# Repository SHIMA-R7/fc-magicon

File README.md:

# FC-MAGICON

Waveshare Core2350B(RP2350B)1枚で作るファミコン用カセット。

ツインファミコン＋ブラウン管での実機表示。[カートリッジ・画面の接写・テスト風景を見る（写真4枚）](docs/photos_20261018.md)。

- PRG・CHR を RP2350B がリアルタイムにエミュレート(マジコン。NROM/CNROM/UNROM/MMC1/MMC3 などをファームで実装)
- NSF 再生(バンク切り替え・WRAM 対応。拡張音源は PWM で46番に混ぜる)
- PC→FC 画面転送(PPU の読み出しに直接応答する FC-PICO 方式)

## 2026-11-08の更新

- **カセットへのPC有線接続なしで更新**：ESP32-C6経由のWi-Fi→USBでファームとFCPVメディアを転送・照合し、DP100による電源再投入で再生。[導入・更新手順](docs/c6-usb-update.md)。
- **SWD経由の導入・復旧**：C6 GPIO6/7を利用し、Wi-Fi経由でOpenOCDから書き込み・照合。[SWD手順](docs/c6-swd-programming.md)。
- **全編8fps映像＋FC本体DAC音声**：約67秒の全編を実機確認。RAM常駐の6502ドライバーが224 CPUサイクル間隔で `$4011` へ書き込み、歌声・伴奏を再生。
- **OLED＋追加パスコンで再試験**：無線更新、全編再生2回、再起動3回の接続に成功。ただし最初の1回はWi-Fi接続に失敗しており、完全な起動安定性やパスコンの効果は未確定。[測定値・確認範囲](docs/wifi-update-validation-20261108.md)。
- 公開対象はソースと検証記録。動画・音声素材、それらを含むファーム、Wi-Fi認証情報は含めません。

## 2026-10-31の更新

- **新基板の元配線で全編動画を再生**：全1,939コマ・8fpsの進行と、FC給電だけでの起動を確認。[検証記録](docs/new_board_video_20261031.md)。
- **動画と本体音源の同時再生**：ユーザー提供MIDIを矩形波2音＋三角波へ変換し、動画と一緒に再生。本体音源の発音はユーザーが確認した。[方式・ビルド手順・確認範囲](docs/native_apu_video_20261031.md)。
- **一時的な横縞への対策**：画面切り替えの制御情報を事前生成してCPUへ高速応答する比較版で、問題の場面の横縞が再現せず、248秒の全編試験を完走。全画素の無欠損や旧基板の故障原因まで保証する結果ではない。
- MIDI、動画、録画、楽曲を含むヘッダー・UF2は公開しない。公開ソースでは自分のMIDIを外部ファイルとして指定する。

## 2026-10-18時点の達成事項

- **単独動画再生の目標達成**：PC非接続のツインファミコンで、全編99秒・8fpsのカラー映像と音声を再生。ユーザーが完成を確認した。著作物である動画素材・音声・それらを含むUF2は公開しない。
- **ESP32-C6無線リモートデスクトップ**は、PCの映像・音声とFC入力をWi-Fi経由でやりとりします。ツインファミコン給電のみでの起動と映像転送を実機で確認しました。[配線・ビルド・4:3全画面設定](docs/wifi-remote-desktop.md)
- **USBリモートデスクトップでブルアカ操作に成功**：FMV（Windows 11）から映像・音声を転送し、入力をPCへ反映。通常のWindowsでは動くのにブルアカでFCパッド／Nanoマウスが効かない問題は、ユーザーが**送信アプリを管理者として実行して解消を確認**した。この環境では送信アプリを右クリック→管理者として実行する。
- **操作機能**：SELECTで通常→中段ズーム（512×480）→最大ズーム（256×240）。FCキーボード対応。NanoのUSBシリアルによるSFCマウス移動・左右クリックも追加し、元のPico向け通信は維持した。
- **終了動作**：受信r2は送信アプリ停止時と切断／受信停止時に、音声を止めて待機画面へ戻る。
- **配布**：[Windows送信アプリr2.3](https://github.com/SHIMA-R7/fc-magicon/releases/tag/usb-sender-r2.3-20261018)、[FMVの使い方](docs/fmv_usb_sender_r2_20261017.md)、[Nanoマウス](docs/nano_sfc_mouse_20261018.md)。送信アプリと受信ファームは別の版番号。
- **映像崩れの切り分け**：同じファームの照合は通り、最小診断ではROM読み出し3508回中不一致0。ユーザーがカセット／基板を動かすと崩れが消えることを確認し、接触状態が強く疑われる。音声・キーボードの処理だけが原因とした途中の見立ては確定していない。接触箇所と長時間安定性は引き続き確認が必要。
- **次の段階**：ESP32-C6による無線転送。現在の修正済み映像・音声との統合、電源容量、逆給電防止を確認してから進める。

[達成状況と実機確認](docs/milestones_20261018.md) ／ [今後の計画](docs/roadmap_after_video_stability_20261015.md)

### 2026-10-13時点の経過（以下の未確認事項の一部は、その後上記まで進展）

- **実機確認**：NEWファミコンで診断画像、F1 Race、スーパーマリオブラザーズが動作。SMB1はユーザーが1-2までプレイし問題なし。MMC3のマリオ3は遊べる段階まで進んだが、下部表示の化けが残る。
- **リモート表示**：実機でPC画面の灰色・全画面表示を確認。高画質カラー・動画・音声の同時動作はまだ実機未確認。
- **オフライン検証**：MMC3のIRQテストと同一入力3,900フレームの比較、カラー動画の連続表示、実際のC音声リングを使った通信負荷試験を追加。エミュから描画位置を得る試験は、実機の成功を保証しない。
- **修正**：MMC3リロード要求の世代管理、リモートのタイル番号保持、12ドットカーソル、マウス感度半減、音声を映像の間に送れる任意の分割プロトコル。
- **未解決**：実機のPPU位置検出・応答期限、タイル圧縮の画質低下と8フレームNT更新中の混在、実機のMMC3 IRQ/CHR更新、カラー・音声・動画の安定性。
- 検証記録：[MMC3](docs/mmc3_sequence_validation_20261013.md)、[動画・音声](docs/remote_video_audio_validation_20261013.md)、[PVの30秒検証](docs/youtube_transfer_30s_20261013.md)。ゲームROMや動画素材は公開しない。
- [先例を参考にした最適化](docs/reference_optimization_20261013.md)：PCのカラー変換を画素同一のまま平均26.9ms→14.8msへ短縮。ネームテーブル/CHRアドレスだけからの位置検出もエミュで確認（実機のDMA経路への接続はまだ）。同じPVを再検証済み。
- 未書込みの実験版：[分割受信・小カーソルのUF2](firmware/out-direct-pio-diagnostic/magicon-remote-full-smallcursor-chunked.uf2)。`remote_pc.py --chunked` はこの新受信ファーム専用。従来プロトコルは引き続き使用できる。

## カートリッジの外観

光沢ラベルを貼ったカートリッジ。開口部からCore2350B2や各操作部へアクセスできる。[実機写真の一覧](docs/photos_20261018.md)。

## 基板と既存機能

- **基板 rev0.2 の設計が完了(2層、DRC エラー0・未接続0)。発注済み（2026-10-10 ユーザー確認）。**
- 発注後の保護対策: [対策・後付け回路・検証手順](docs/post_order_protection.md)。保護版ファームは `firmware/out-protected/`。現物での電源・バス波形検証は未実施。
- ファームウェア: 動作確認用の `bus_test`(CPU バスでテスト ROM を返して音を鳴らす)と `chr_test`(PPU に CHR を返して画面に格子模様を出す)、
  マジコン本体の `magicon`(.nes を動かす。NROM/MMC1/UxROM/CNROM/MMC3/AxROM、PRG + CHR 384KB まで)を作成、ビルド済み。各モードの実機確認範囲は上記を参照。[`firmware/`](firmware/README.md)
- rev0.1 からの変更: USB の予備ランド(J6)、拡張音源の音量用の半固定抵抗 VR1(KOA KVSF637AC104)を追加、
  電源・音声の配線を太くした(+5V 0.8mm、VBUS 0.6mm、GND 0.5mm、+3V3 0.4mm、音声 0.4mm)、J5 の 12〜14番を GND に。
- ガーバー: [`kicad/FC-MAGICON_gerber_r0.2.zip`](kicad/FC-MAGICON_gerber_r0.2.zip)(発注の指定は下の「基板の発注」)
- 仕様書: [`docs/hardware_spec.pdf`](docs/hardware_spec.pdf)(rev0.2)

| 正面(部品面、本体の手前) | 背面 |
|---|---|
|  |  |

## ファイル

| パス | 内容 |
|---|---|
| `kicad/gen_schematic.py` | 回路図の生成スクリプト(`python gen_schematic.py` → `FC-MAGICON.kicad_sch`) |
| `kicad/gen_footprints.py` | カセット端子と半固定抵抗(KOA KVSF637A)のフットプリントを生成 |
| `kicad/build_pcb.py` | 基板の部品配置(`place`)、配線の取り込みと GND ベタ(`import`)、一部の配線のやり直し(`reroute`) |
| `kicad/route.py` | Freerouting で自動配線(線幅のクラスを付ける) |
| `kicad/add_part.py` / `sync_nets.py` / `hand_route.py` | 配線済みの基板に部品を足す / パッドのネットを回路図に合わせる / 1本だけ手で引く |
| `kicad/export_gerbers.ps1` | DRC がエラー 0 のときだけガーバーを出して zip にする |
| `kicad/bom.py`, `print_bom.ps1` | 部品表(`bom.csv`)の作成と印刷 |
| `kicad/print_core2350b_pinmap.ps1`, `print_fit_check.ps1` | Core2350B のピン照合シート、実寸の現物合わせシートの印刷 |
| `kicad/check_nets.py`, `drc_summary.py` | 回路図の簡易チェック、DRC レポートの集計 |
| `3d/` | 基板の STEP(`FC-MAGICON_r0.2_parts.step` 部品あり / `_board.step` 基板だけ / `FC-MAGICON.step` 部品あり版を Autodesk で読み込んで書き出し直したもの)。`make_models.py` → `export_step.py`(KiCad の Python)で作り直す。原点は基板の左上、Y は上向き(基板は Y 0〜-65.8) |
| `kicad/print_part_guide.ps1` | 部品案内図(表・裏、原寸)の印刷 |
| `case/label/` | カセット表面のシール(`make_label.py` → `label.png`、`print_label.ps1` で A4 に印刷)。99 x 60.6mm、ケースの穴(J3/J5/J6/VR1/SW/Core2350B2)は原寸。L 判の光沢紙にきれいに刷る時は `make_label.py --px 48 --out label_print.png` → `powershell.exe -File print_label_photo.ps1`(光沢紙・写真品質) |
| `case/*.py` | ケースの元データ(下記)の寸法を調べたスクリプトと、基板の部品の占有範囲(`parts.json`) |
| `docs/` | ハードウェア仕様書(`build_spec.py` と `kicad/gen_spec_tables.py` で作る) |

KiCad 10、Freerouting 2.4.1 を使用。KiCad の Python(pcbnew)で実行するスクリプトと、ふつうの Python で実行するスクリプトがある(各ファイルの先頭に記載)。

## ライセンス

独自コードはMIT(`LICENSE`)。第三者のエミュレーターや検証用パッチはそれぞれのライセンスに従う。[第三者コードと検証コア](firmware/sim/THIRD_PARTY.md)を参照。外形の参考にしたデータ(下記「カセット外形の参考データ」)はこのリポジトリに含めていない。

## ピン割り当て

| GPIO | 信号 | カセット端子 | 備考 |
|---|---|---|---|
| 0-7 | CPU D0-D7 | 43,42,41,40,39,38,37,36 | |
| 8-22 | CPU A0-A14 | 13,12,11,10,9,8,7,6,5,4,3,2,33,34,35 | A0から連続 |
| 23 | /ROMSEL | 44 | |
| 24 | CPU R/W | 14 | |
| 25 | M2 | 32 | |
| 26-33 | PPU AD0-AD7 | 26,27,28,29,60,59,58,57 | /RD直前はアドレス下位、その後データ |
| 34-38 | PPU A8-A12 | 51,52,53,54,55 | 26-38で13ビット連続 |
| 39 | (基板上LED) | — | バスに使わない |
| 40 | PPU /RD | 17 | U2(74LVC245)経由 |
| 41 | PPU /WR | 47 | U2経由 |
| 42 | PPU A13 | 56 | U2経由 |
| 43 | CIRAM A10 出力 | 18 | JP1を閉じたとき |
| 44 | 拡張音源 PWM | 46へ混ぜる | |
| 45 | /IRQ 駆動 | 15 | Q1(NPN)でオープンコレクタ |
| 46 | 本体5V検出 | 30,31 を分圧 | Highになるまでバスに出力しない |

- PIO の32本窓: CPU 用ブロックは GPIO0-31、PPU 用ブロックは GPIO16-47。
- GPIO0-38 は 5V トレラント。GPIO40-47 は ADC 兼用で **5V 非トレラント**。
- PPU A0-A7(19-25, 50番)はつながない。
- CIRAM /CE(48)は /A13(49)に直結(R1 0Ω)。
- ミラーリング: JP1(MCU)/ JP2(A10=垂直)/ JP3(A11=水平)のどれか1つだけ閉じる。

## テスト用のランド(2.54mmピッチ、ピンヘッダー・ソケットどちらも可)

基板は規格(56.8mm)より 9mm 高い(90 × 65.8mm)。

**J4: カセット60ピン全部(2x30)** — 差し込み部のすぐ上(2026-09-26、2層に収めるため上辺から移動)
各列がカセット端子の真上にあり、端子から J4 まではほぼ真上への短い配線。上の列 = 31〜60番、下の列 = 1〜30番。
部品面(本体の手前)から見て左端が 1/31番、右端が 30/60番(シルクに列番号あり)。
RP2350 では使わない PPU A0-A7(19〜25番、50番)も出している。

**J5: 基板内部の信号(2x8)** — 上辺
部品面から見て左端が 1/2番。奇数番 = 下の列、偶数番 = 上の列。

| ピン | 信号 | ピン | 信号 |
|---|---|---|---|
| 1 | PPU /RD(3.3V、U2の後) | 2 | PPU /WR(3.3V) |
| 3 | PPU A13(3.3V) | 4 | CIRAM A10(GPIO43の出力) |
| 5 | 拡張音源 PWM(GPIO44) | 6 | PWM の RC フィルタの後 |
| 7 | /IRQ 駆動(GPIO45) | 8 | 本体5V検出(GPIO46) |
| 9 | +3.3V | 10 | VBUS(モジュールの電源) |
| 11 | CIRAM A10(18番へ行く線) | 12 | ライン出力(47kの前) |
| 13 | Q1 ベース | 14 | ライン出力(100Ωの後) |
| 15 | GND | 16 | GND |

TP1〜TP5(/RD、D0、M2、/ROMSEL、GND)はオシロのプローブ用。

## 基板発注前に確認すること

1. ~~**カセット端子の電源・音声・制御ピン。**~~ → 2026-09-26 ユーザーが麻雀カセット・本体で確認、問題なし。 信号線51本はダンパー(`../FC`)で実機確認済み。
   1,16(GND)・30,31(+5V)・15(/IRQ)・18(CIRAM A10)・45,46(音声)・47(/WR)・48(CIRAM /CE)・49(/A13)は
   nesdev の資料によるので、麻雀カセットと本体で導通を確認する。
2. ~~**45/46 の向き。**~~ → 2026-09-26 確認済み。 本体(HVC-CPU-07)で、どちらが 2A03 の音声回路につながっているか確認する。
3. ~~**本体の /IRQ プルアップの有無。**~~ → 2026-09-26 確認済み。 無ければ R6(10k)を実装する。
4. ~~Core2350B のヘッダー配置~~ → 2026-09-26 に照合シート(`kicad/print_core2350b_pinmap.ps1`)で、実物のシルクと全ピン一致を確認した。
   25.4mm角、外周2列、2.54mmピッチ。左・下・右・上がそれぞれ P1・P3・P4・P2。
5. ~~カセットの基板厚とエッジの寸法~~ → 参考データ(下記)から、厚み 1.2mm・差し込み部 78.4 × 10.7mm。
   正確に作るのはスロットに刺さる部分だけでよい。残りの外形は自由にし、ケースは3Dプリント(Bambu P1S)で作る。
6. **試作での実測。** PPU の /RD が下がってからデータを返すまでの時間。仮配線はせず、この基板(TP1〜TP5)で測る方針に変更。

## 基板の発注(JLCPCB)

`kicad/FC-MAGICON_gerber_r0.1.zip` をアップロードする(`kicad/export_gerbers.ps1` で作り直せる。DRC にエラーがあると止まる)。

| 項目 | 指定 |
|---|---|
| 層数 | 2 |
| 厚み | **1.2mm**(ファミコンのスロットに合わせる。1.6mm は入らない) |
| 金メッキ端子 | Gold Fingers: Yes |
| 面取り | 差し込み側 45°(finger chamfer) |
| 表面処理 | 金メッキ端子と組み合わせられるもの(発注画面で ENIG 指定が必要か確認する) |
| 数量 | 5枚(最小) |

- 外形は 90 × 65.8mm。差し込み部(78.4 × 10.7mm)の両脇は切り欠き。
- 端子部のレジストは、端子の上端から 0.6mm 上で止めてある(付け根側の配線はレジストで覆う)。

## カセット外形の参考データ(`ref/`)

| 出典 | ライセンス | 中身 |
|---|---|---|
| [Gumball2415/NES-Famicom-Cartridge-Dimensions](https://github.com/Gumball2415/NES-Famicom-Cartridge-Dimensions) | TAPR OHL 1.0 | HVC-TGROM-01 / HVC-CNROM-256K-01 の外形(KiCad)と FreeCAD 3Dモデル(.FCStd、STEP書き出し可) |
| [Keitark/fc-rom-vomitter](https://github.com/Keitark/fc-rom-vomitter) | ハード: CC BY-SA 4.0 | 60ピンのエッジのフットプリントと、実際に製造したファミコン用基板 |

- 標準のファミコン基板: 幅 90.0mm × 高さ 56.8mm(差し込み部 78.4 × 10.7mm を含む)、**厚み 1.2mm**、ピッチ 2.54mm。
- 市販カセットは 1〜30番がラベル面(本体の手前)。この基板は部品面(F.Cu)を手前に向けたので、F.Cu = 1〜30番、B.Cu = 31〜60番。
- ピン配置は fc-rom-vomitter の表とも一致した(30/31=+5V、1/16=GND、45=本体からの音声、46=本体へ戻す音声、48/49=/A13)。
- ファイルをそのまま流用する場合は、元のライセンスに従うこと。寸法(事実)を参照して自作するならその限りではない。

## ケース(3Dプリント)の元データ

[printables 860420「Nintendo Famicom Cartridge Shell」](https://www.printables.com/model/860420-nintendo-famicom-cartridge-shell)(CC BY 4.0)。
これは [masible/famicom-everdrive-n8-shell-with-usb](https://github.com/masible/famicom-everdrive-n8-shell-with-usb)(hadessuk、CC BY)を
標準の基板向けにしたリミックスで、さらに元は Blackchamber の [Thingiverse 117607](https://www.thingiverse.com/thing:117607/)(CC BY)。
改変版を公開するときは、この3つの作者の表記を残す。

## 注意

- USB だけで給電しているときに本体のバスへ出力すると、電源の入っていない本体に電流が逆流する。
  ファームは `FC_5V_SENSE` が High になるまで、全ピンを入力にしておく。
- RP2350 のエラッタ E9 に注意。バスのピンでは内部プルダウンを使わない。
- Q1 の 2SC1815 は、平らな面から見て E-C-B。

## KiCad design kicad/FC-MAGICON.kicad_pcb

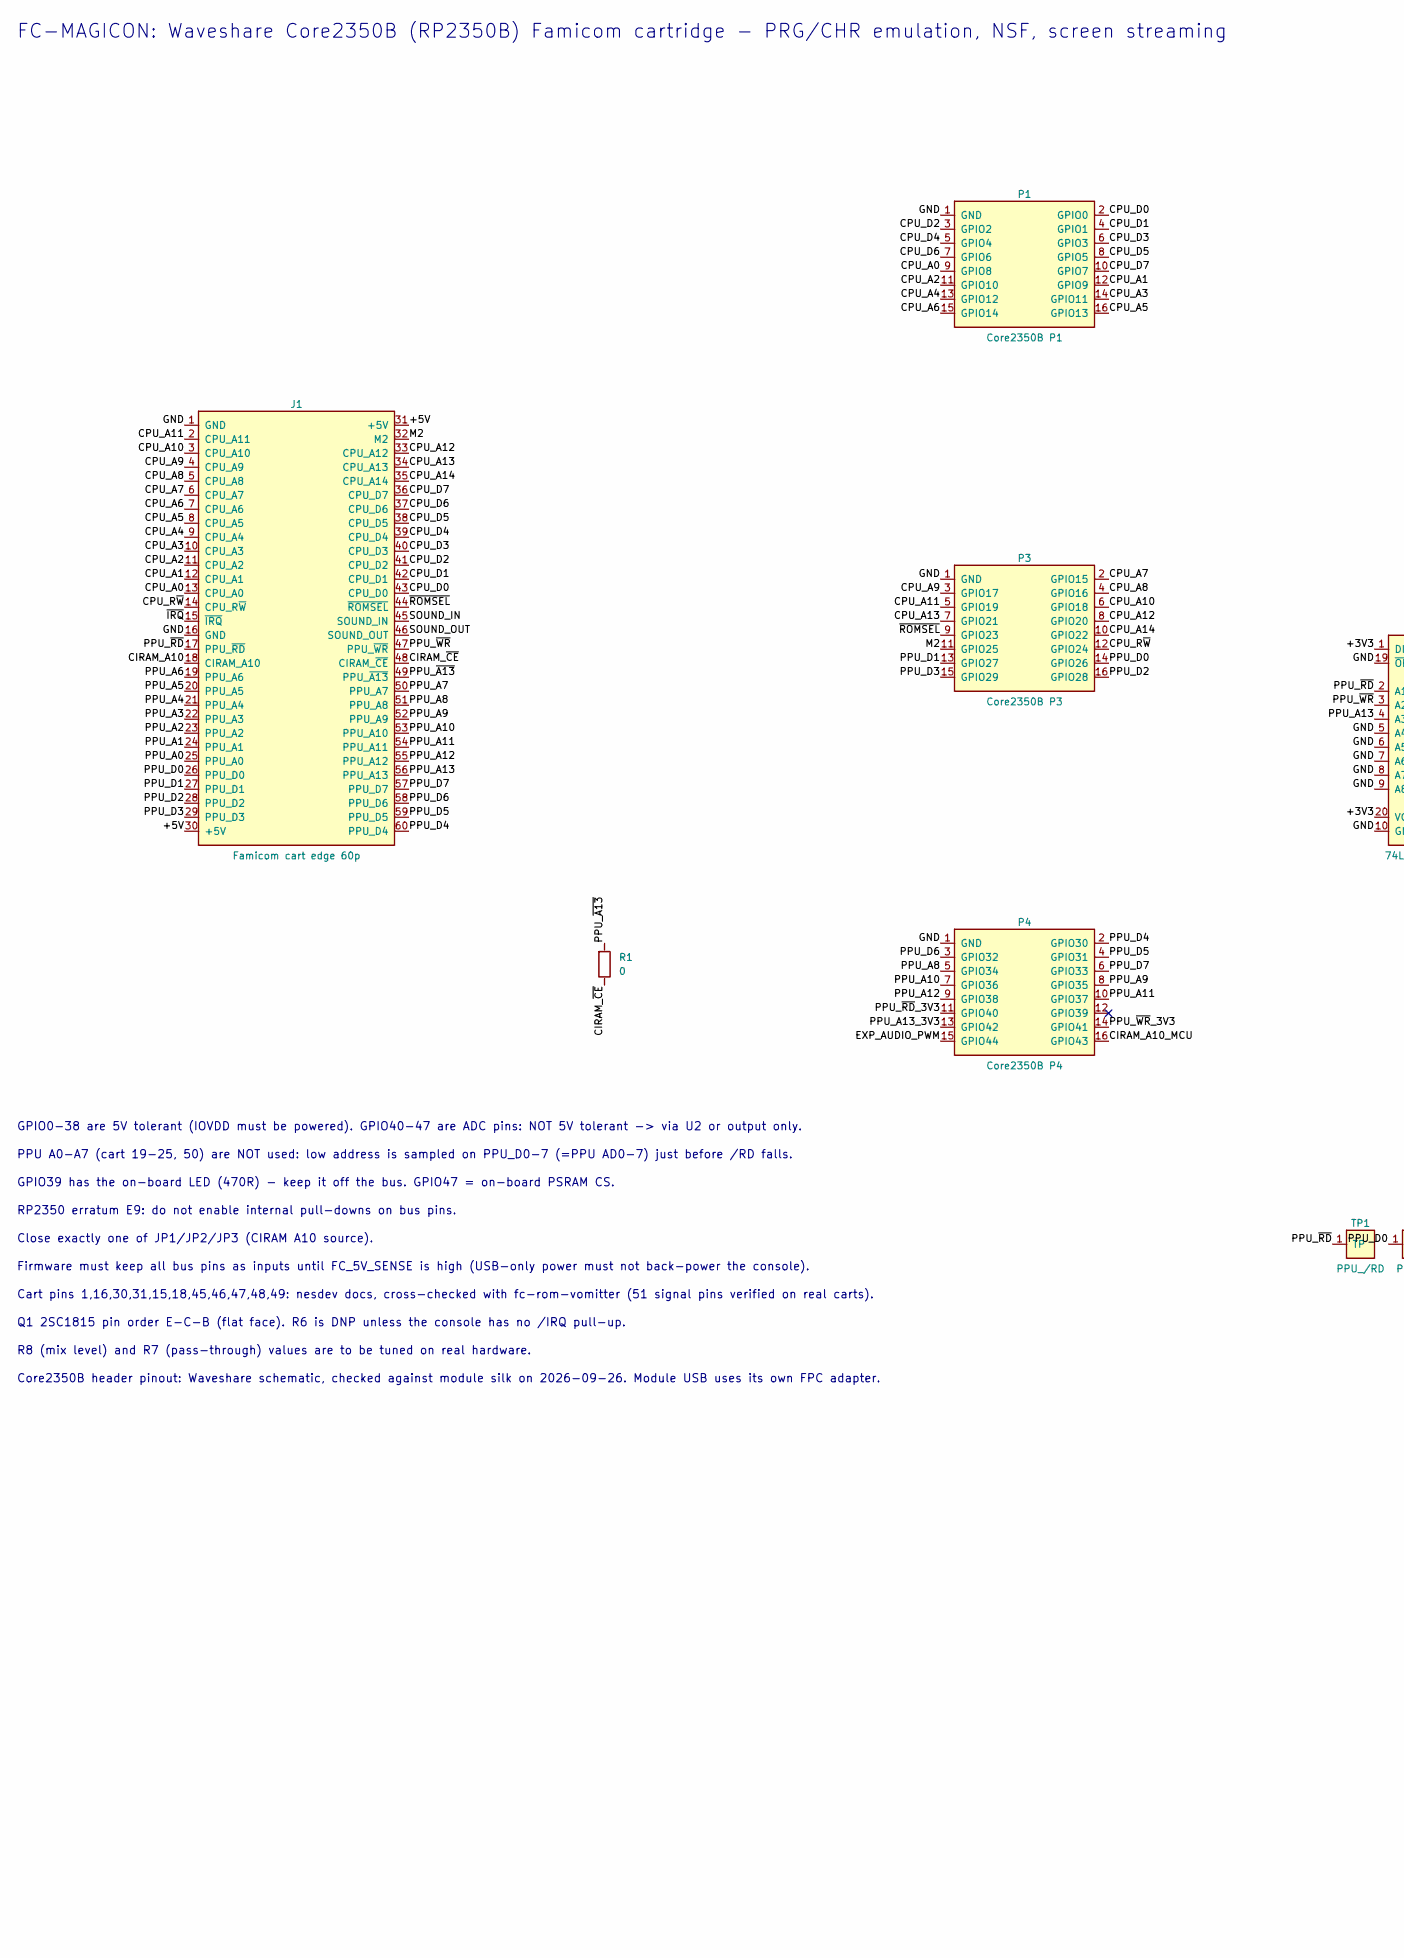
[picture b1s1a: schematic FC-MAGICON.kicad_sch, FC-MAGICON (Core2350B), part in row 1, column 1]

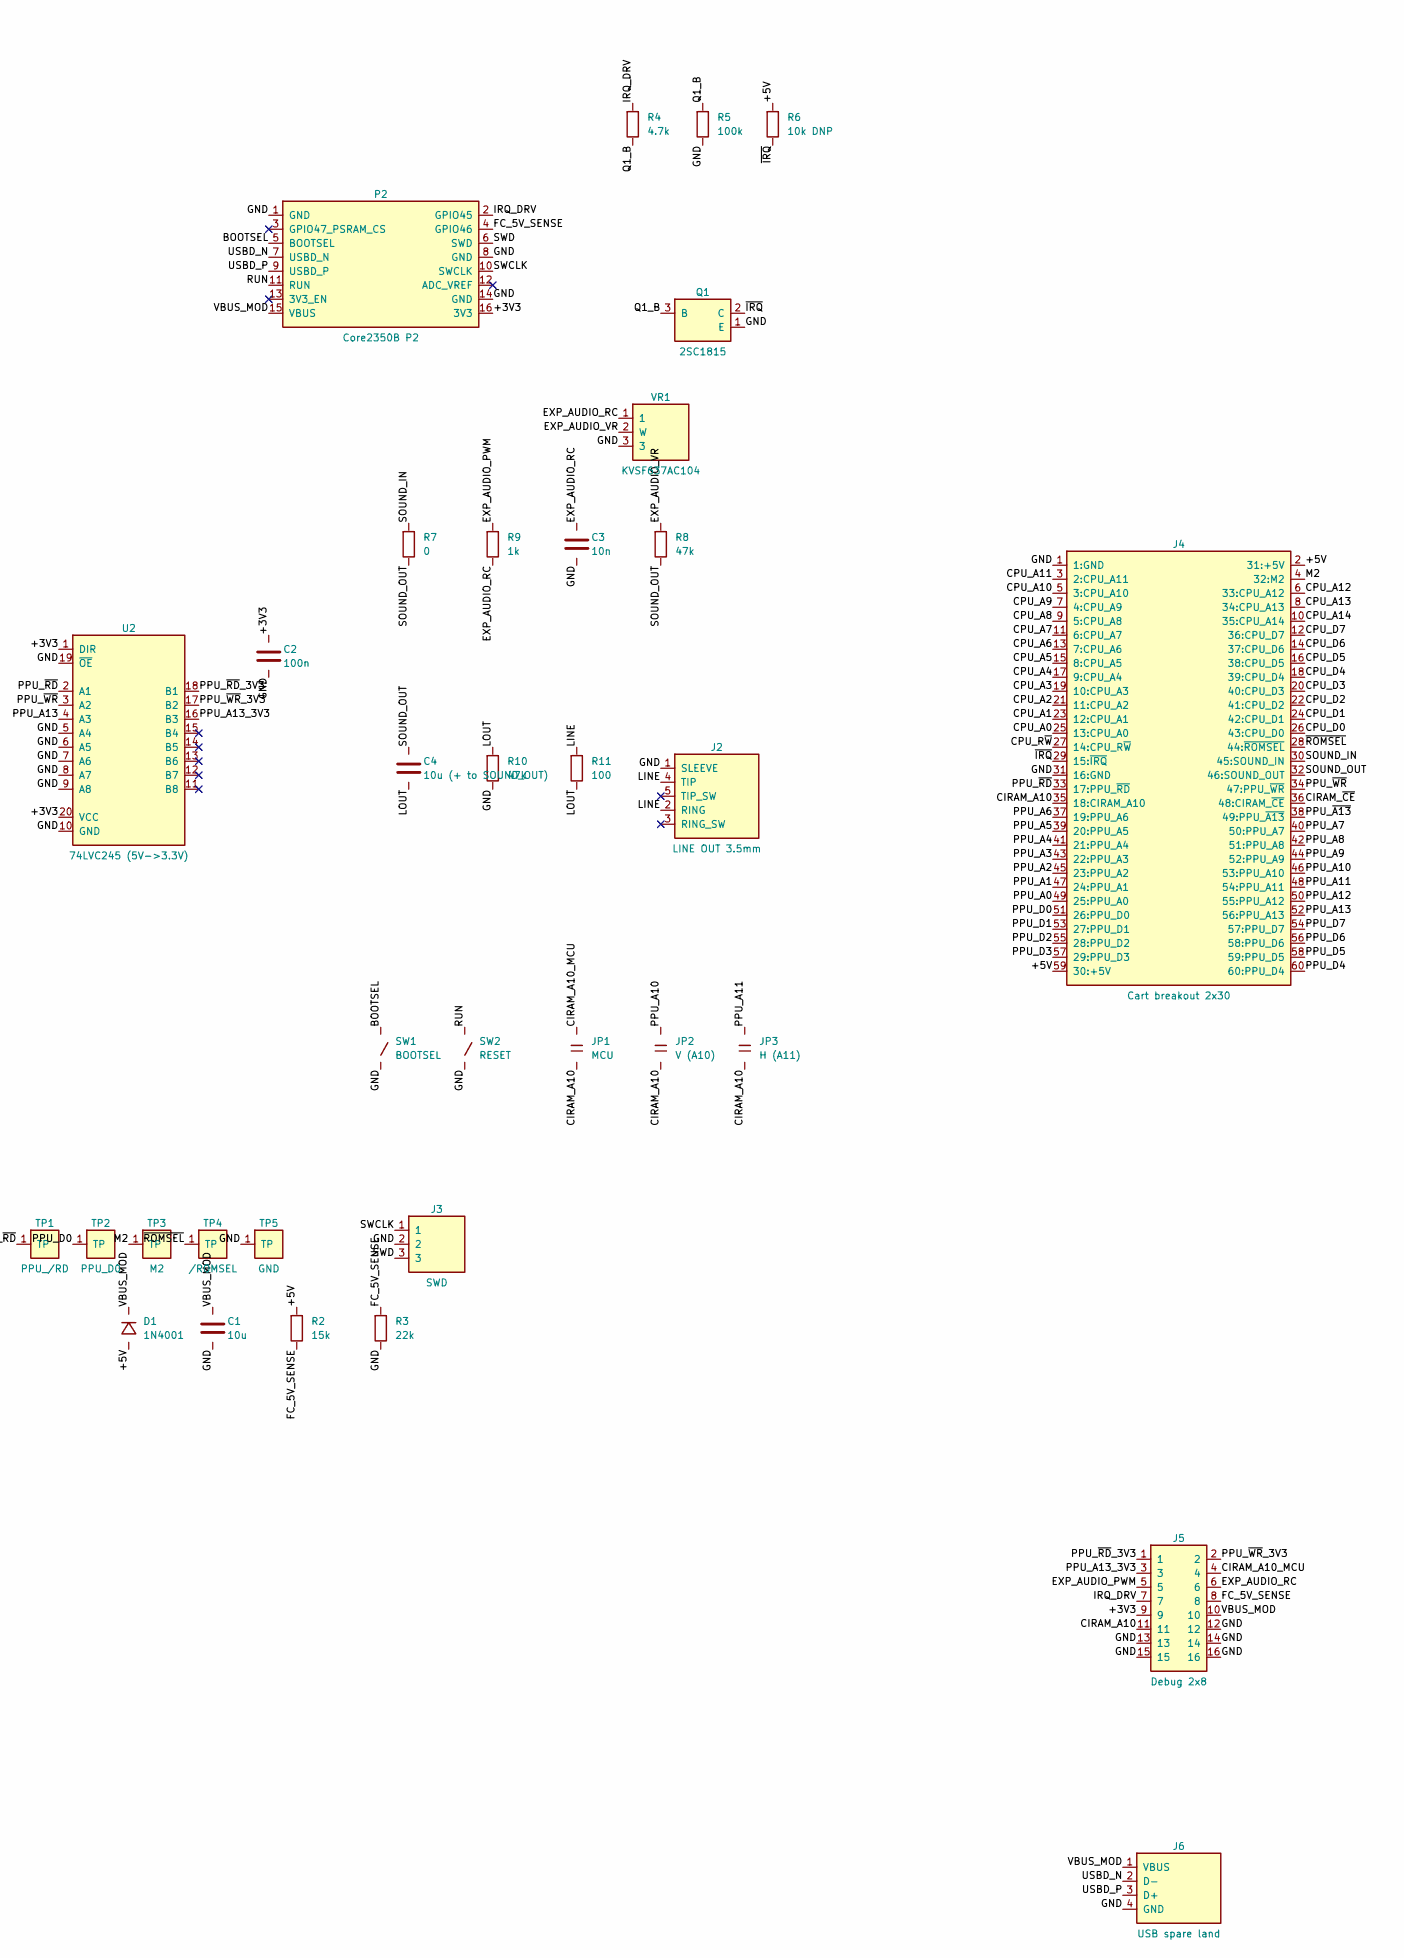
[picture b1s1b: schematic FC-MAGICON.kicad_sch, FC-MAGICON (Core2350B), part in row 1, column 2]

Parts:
C1: 10u; CP_Radial_D5.0mm_P2.00mm
C2: 100n; C_Disc_D3.0mm_W1.6mm_P2.50mm
C3: 10n; C_Disc_D3.0mm_W1.6mm_P2.50mm
C4: 10u (+ to SOUND_OUT); CP_Radial_D5.0mm_P2.00mm
D1: 1N4001; D_DO-41_SOD81_P7.62mm_Horizontal
J1: Famicom cart edge 60p; FC_Cart_Edge_60
J2: LINE OUT 3.5mm; PJ-324M
J3: SWD; PinHeader_1x03_P2.54mm_Vertical
J4: Cart breakout 2x30; PinHeader_2x30_P2.54mm_Vertical
J5: Debug 2x8; PinHeader_2x08_P2.54mm_Vertical
J6: USB spare land; PinHeader_1x04_P2.54mm_Vertical
JP1: MCU; SolderJumper-2_P1.3mm_Open_RoundedPad1.0x1.5mm
JP2: V (A10); SolderJumper-2_P1.3mm_Open_RoundedPad1.0x1.5mm
JP3: H (A11); SolderJumper-2_P1.3mm_Open_RoundedPad1.0x1.5mm
P1: Core2350B P1; PinHeader_2x08_P2.54mm_Vertical
P2: Core2350B P2; PinHeader_2x08_P2.54mm_Vertical
P3: Core2350B P3; PinHeader_2x08_P2.54mm_Vertical
P4: Core2350B P4; PinHeader_2x08_P2.54mm_Vertical
Q1: 2SC1815; TO-92_Inline_Wide
R1, R7: 0; R_Axial_DIN0207_L6.3mm_D2.5mm_P7.62mm_Horizontal
R2: 15k; R_Axial_DIN0207_L6.3mm_D2.5mm_P7.62mm_Horizontal
R3: 22k; R_Axial_DIN0207_L6.3mm_D2.5mm_P7.62mm_Horizontal
R4: 4.7k; R_Axial_DIN0207_L6.3mm_D2.5mm_P7.62mm_Horizontal
R5: 100k; R_Axial_DIN0207_L6.3mm_D2.5mm_P7.62mm_Horizontal
R6: 10k DNP; R_Axial_DIN0207_L6.3mm_D2.5mm_P7.62mm_Horizontal
R8, R10: 47k; R_Axial_DIN0207_L6.3mm_D2.5mm_P7.62mm_Horizontal
R9: 1k; R_Axial_DIN0207_L6.3mm_D2.5mm_P7.62mm_Horizontal
R11: 100; R_Axial_DIN0207_L6.3mm_D2.5mm_P7.62mm_Horizontal
SW1: BOOTSEL; SW_PUSH_6mm
SW2: RESET; SW_PUSH_6mm
TP1: PPU_/RD; TestPoint_THTPad_D1.5mm_Drill0.7mm
TP2: PPU_D0; TestPoint_THTPad_D1.5mm_Drill0.7mm
TP3: M2; TestPoint_THTPad_D1.5mm_Drill0.7mm
TP4: /ROMSEL; TestPoint_THTPad_D1.5mm_Drill0.7mm
TP5: GND; TestPoint_THTPad_D1.5mm_Drill0.7mm
U2: 74LVC245 (5V->3.3V); DIP-20_W7.62mm
VR1: KVSF637AC104; KOA_SF6_637A

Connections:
/+3V3: C2.1, J5.9, P2.16 (3V3), U2.1 (DIR), U2.20 (VCC)
/+5V: D1.2, J1.30 (+5V), J1.31 (+5V), J4.2 (31:+5V), J4.59 (30:+5V), R2.1, R6.1
/BOOTSEL: P2.5 (BOOTSEL), SW1.1
/CIRAM_A10: J1.18 (CIRAM_A10), J4.35 (18:CIRAM_A10), J5.11, JP1.2, JP2.2, JP3.2
/CIRAM_A10_MCU: J5.4, JP1.1, P4.16 (GPIO43)
/CIRAM_~CE: J1.48 (CIRAM_~CE), J4.36 (48:CIRAM_~CE), R1.2
/CPU_A0: J1.13 (CPU_A0), J4.25 (13:CPU_A0), P1.9 (GPIO8)
/CPU_A1: J1.12 (CPU_A1), J4.23 (12:CPU_A1), P1.12 (GPIO9)
/CPU_A2: J1.11 (CPU_A2), J4.21 (11:CPU_A2), P1.11 (GPIO10)
/CPU_A3: J1.10 (CPU_A3), J4.19 (10:CPU_A3), P1.14 (GPIO11)
/CPU_A4: J1.9 (CPU_A4), J4.17 (9:CPU_A4), P1.13 (GPIO12)
/CPU_A5: J1.8 (CPU_A5), J4.15 (8:CPU_A5), P1.16 (GPIO13)
/CPU_A6: J1.7 (CPU_A6), J4.13 (7:CPU_A6), P1.15 (GPIO14)
/CPU_A7: J1.6 (CPU_A7), J4.11 (6:CPU_A7), P3.2 (GPIO15)
/CPU_A8: J1.5 (CPU_A8), J4.9 (5:CPU_A8), P3.4 (GPIO16)
/CPU_A9: J1.4 (CPU_A9), J4.7 (4:CPU_A9), P3.3 (GPIO17)
/CPU_A10: J1.3 (CPU_A10), J4.5 (3:CPU_A10), P3.6 (GPIO18)
/CPU_A11: J1.2 (CPU_A11), J4.3 (2:CPU_A11), P3.5 (GPIO19)
/CPU_A12: J1.33 (CPU_A12), J4.6 (33:CPU_A12), P3.8 (GPIO20)
/CPU_A13: J1.34 (CPU_A13), J4.8 (34:CPU_A13), P3.7 (GPIO21)
/CPU_A14: J1.35 (CPU_A14), J4.10 (35:CPU_A14), P3.10 (GPIO22)
/CPU_D0: J1.43 (CPU_D0), J4.26 (43:CPU_D0), P1.2 (GPIO0)
/CPU_D1: J1.42 (CPU_D1), J4.24 (42:CPU_D1), P1.4 (GPIO1)
/CPU_D2: J1.41 (CPU_D2), J4.22 (41:CPU_D2), P1.3 (GPIO2)
/CPU_D3: J1.40 (CPU_D3), J4.20 (40:CPU_D3), P1.6 (GPIO3)
/CPU_D4: J1.39 (CPU_D4), J4.18 (39:CPU_D4), P1.5 (GPIO4)
/CPU_D5: J1.38 (CPU_D5), J4.16 (38:CPU_D5), P1.8 (GPIO5)
/CPU_D6: J1.37 (CPU_D6), J4.14 (37:CPU_D6), P1.7 (GPIO6)
/CPU_D7: J1.36 (CPU_D7), J4.12 (36:CPU_D7), P1.10 (GPIO7)
/CPU_R~W: J1.14 (CPU_R~W), J4.27 (14:CPU_R~W), P3.12 (GPIO24)
/EXP_AUDIO_PWM: J5.5, P4.15 (GPIO44), R9.1
/EXP_AUDIO_RC: C3.1, J5.6, R9.2, VR1.1
/EXP_AUDIO_VR: R8.1, VR1.2 (W)
/FC_5V_SENSE: J5.8, P2.4 (GPIO46), R2.2, R3.1
/GND: C1.2, C2.2, C3.2, J1.1 (GND), J1.16 (GND), J2.1 (SLEEVE), J3.2, J4.1 (1:GND), J4.31 (16:GND), J5.12, J5.13, J5.14, J5.15, J5.16, J6.4 (GND), P1.1 (GND), P2.1 (GND), P2.8 (GND), P2.14 (GND), P3.1 (GND), P4.1 (GND), Q1.1 (E), R3.2, R5.2, R10.2, SW1.2, SW2.2, TP5.1, U2.5 (A4), U2.6 (A5), U2.7 (A6), U2.8 (A7), U2.9 (A8), U2.10 (GND), U2.19 (~OE), VR1.3
/IRQ_DRV: J5.7, P2.2 (GPIO45), R4.1
/LINE: J2.2 (RING), J2.4 (TIP), R11.1
/LOUT: C4.2, R10.1, R11.2
/M2: J1.32 (M2), J4.4 (32:M2), P3.11 (GPIO25), TP3.1
/PPU_A0: J1.25 (PPU_A0), J4.49 (25:PPU_A0)
/PPU_A1: J1.24 (PPU_A1), J4.47 (24:PPU_A1)
/PPU_A2: J1.23 (PPU_A2), J4.45 (23:PPU_A2)
/PPU_A3: J1.22 (PPU_A3), J4.43 (22:PPU_A3)
/PPU_A4: J1.21 (PPU_A4), J4.41 (21:PPU_A4)
/PPU_A5: J1.20 (PPU_A5), J4.39 (20:PPU_A5)
/PPU_A6: J1.19 (PPU_A6), J4.37 (19:PPU_A6)
/PPU_A7: J1.50 (PPU_A7), J4.40 (50:PPU_A7)
/PPU_A8: J1.51 (PPU_A8), J4.42 (51:PPU_A8), P4.5 (GPIO34)
/PPU_A9: J1.52 (PPU_A9), J4.44 (52:PPU_A9), P4.8 (GPIO35)
/PPU_A10: J1.53 (PPU_A10), J4.46 (53:PPU_A10), JP2.1, P4.7 (GPIO36)
/PPU_A11: J1.54 (PPU_A11), J4.48 (54:PPU_A11), JP3.1, P4.10 (GPIO37)
/PPU_A12: J1.55 (PPU_A12), J4.50 (55:PPU_A12), P4.9 (GPIO38)
/PPU_A13: J1.56 (PPU_A13), J4.52 (56:PPU_A13), U2.4 (A3)
/PPU_A13_3V3: J5.3, P4.13 (GPIO42), U2.16 (B3)
/PPU_D0: J1.26 (PPU_D0), J4.51 (26:PPU_D0), P3.14 (GPIO26), TP2.1
/PPU_D1: J1.27 (PPU_D1), J4.53 (27:PPU_D1), P3.13 (GPIO27)
/PPU_D2: J1.28 (PPU_D2), J4.55 (28:PPU_D2), P3.16 (GPIO28)
/PPU_D3: J1.29 (PPU_D3), J4.57 (29:PPU_D3), P3.15 (GPIO29)
/PPU_D4: J1.60 (PPU_D4), J4.60 (60:PPU_D4), P4.2 (GPIO30)
/PPU_D5: J1.59 (PPU_D5), J4.58 (59:PPU_D5), P4.4 (GPIO31)
/PPU_D6: J1.58 (PPU_D6), J4.56 (58:PPU_D6), P4.3 (GPIO32)
/PPU_D7: J1.57 (PPU_D7), J4.54 (57:PPU_D7), P4.6 (GPIO33)
/PPU_~A13: J1.49 (PPU_~A13), J4.38 (49:PPU_~A13), R1.1
/PPU_~RD: J1.17 (PPU_~RD), J4.33 (17:PPU_~RD), TP1.1, U2.2 (A1)
/PPU_~RD_3V3: J5.1, P4.11 (GPIO40), U2.18 (B1)
/PPU_~WR: J1.47 (PPU_~WR), J4.34 (47:PPU_~WR), U2.3 (A2)
/PPU_~WR_3V3: J5.2, P4.14 (GPIO41), U2.17 (B2)
/Q1_B: Q1.3 (B), R4.2, R5.1
/RUN: P2.11 (RUN), SW2.1
/SOUND_IN: J1.45 (SOUND_IN), J4.30 (45:SOUND_IN), R7.1
/SOUND_OUT: C4.1, J1.46 (SOUND_OUT), J4.32 (46:SOUND_OUT), R7.2, R8.2
/SWCLK: J3.1, P2.10 (SWCLK)
/SWD: J3.3, P2.6 (SWD)
/USBD_N: J6.2 (D-), P2.7 (USBD_N)
/USBD_P: J6.3 (D+), P2.9 (USBD_P)
/VBUS_MOD: C1.1, D1.1, J5.10, J6.1 (VBUS), P2.15 (VBUS)
/~IRQ: J1.15 (~IRQ), J4.29 (15:~IRQ), Q1.2 (C), R6.2
/~ROMSEL: J1.44 (~ROMSEL), J4.28 (44:~ROMSEL), P3.9 (GPIO23), TP4.1

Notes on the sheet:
FC-MAGICON: Waveshare Core2350B (RP2350B) Famicom cartridge - PRG/CHR emulation, NSF, screen streaming
GPIO0-38 are 5V tolerant (IOVDD must be powered). GPIO40-47 are ADC pins: NOT 5V tolerant -> via U2 or output only.
PPU A0-A7 (cart 19-25, 50) are NOT used: low address is sampled on PPU_D0-7 (=PPU AD0-7) just before /RD falls.
GPIO39 has the on-board LED (470R) - keep it off the bus. GPIO47 = on-board PSRAM CS.
RP2350 erratum E9: do not enable internal pull-downs on bus pins.
Close exactly one of JP1/JP2/JP3 (CIRAM A10 source).
Firmware must keep all bus pins as inputs until FC_5V_SENSE is high (USB-only power must not back-power the console).
Cart pins 1,16,30,31,15,18,45,46,47,48,49: nesdev docs, cross-checked with fc-rom-vomitter (51 signal pins verified on real carts).
Q1 2SC1815 pin order E-C-B (flat face). R6 is DNP unless the console has no /IRQ pull-up.
R8 (mix level) and R7 (pass-through) values are to be tuned on real hardware.
Core2350B header pinout: Waveshare schematic, checked against module silk on 2026-09-26. Module USB uses its own FPC adapter.

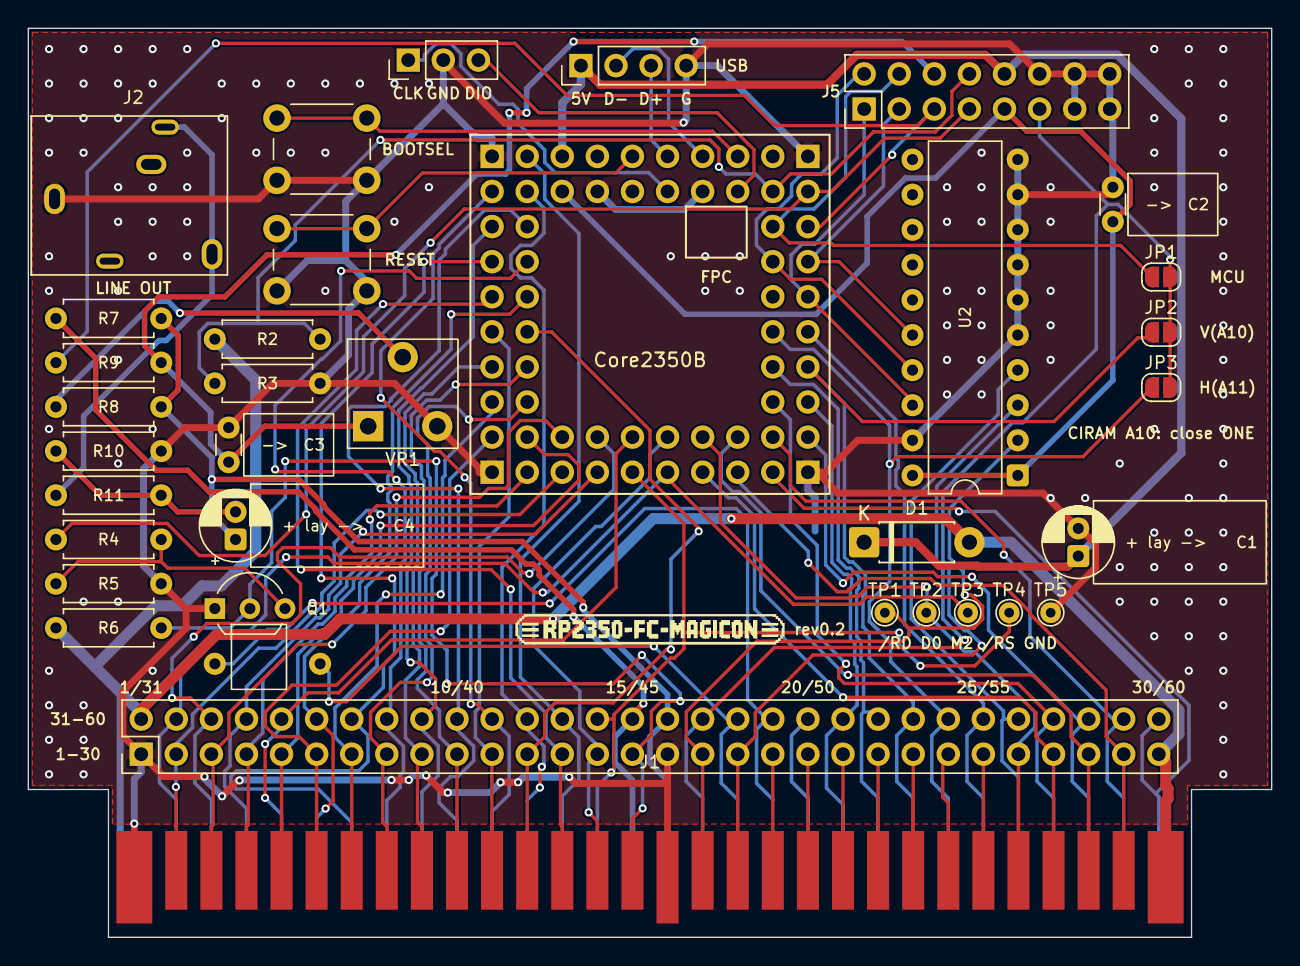
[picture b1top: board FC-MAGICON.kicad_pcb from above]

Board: 2 copper layers, 90.0 x 65.8 mm, 39 parts (1 on the bottom side), 78 nets.

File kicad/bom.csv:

部品,数,記号,フットプリント,メモ
10µF 電解,1,C1,CP_Radial_D5.0mm_P2.00mm,16V以上、φ5 ピッチ2mm
100nF セラミック,1,C2,C_Disc_D3.0mm_W1.6mm_P2.50mm,U2 のパスコン
10nF セラミック,1,C3,C_Disc_D3.0mm_W1.6mm_P2.50mm,PWM の RC フィルタ
10µF 電解,1,C4,CP_Radial_D5.0mm_P2.00mm,φ5 ピッチ2mm。+側=SOUND_OUT(四角パッド)。ライン出力の直流カット。1µFフィルムでも可
1N4001〜1N4007(ショットキー 1A があればそちら),1,D1,D_DO-41_SOD81_P7.62mm_Horizontal,本体5V→モジュール。USB給電時の逆流防止。省略不可
PJ-324M,1,J2,PJ-324M,3.5mm ステレオジャック(SHVC-SOUND-ESP32 と同じ)
ピンヘッダー 1x3,1,J3,PinHeader_1x03_P2.54mm_Vertical,SWD(debugprobe の Pico 用)
ピンヘッダー or ピンソケット 2x30,1,J4,PinHeader_2x30_P2.54mm_Vertical,カセット60ピンのブレイクアウト。必要な時だけでもよい
ピンヘッダー 2x8,1,J5,PinHeader_2x08_P2.54mm_Vertical,デバッグ用(内部信号)
ピンヘッダー 1x4(任意),1,J6,PinHeader_1x04_P2.54mm_Vertical,USB の予備ランド(5V/D-/D+/GND)。FPC 側と同時に機器をつながない
2SC1815,1,Q1,TO-92_Inline_Wide,TO-92 NPN。足は平らな面から E-C-B。他の小信号NPNでも可(足順に注意)。下(J4 側)へ倒して付ける
0Ω(ジャンパー線でも可),1,R1,R_Axial_DIN0207_L6.3mm_D2.5mm_P7.62mm_Horizontal,CIRAM /CE ← /A13。裏面に付ける(表は Q1 を倒す場所)。表の足先は短く切る
15kΩ 1/4W,1,R2,R_Axial_DIN0207_L6.3mm_D2.5mm_P7.62mm_Horizontal,
22kΩ 1/4W,1,R3,R_Axial_DIN0207_L6.3mm_D2.5mm_P7.62mm_Horizontal,
4.7kΩ 1/4W,1,R4,R_Axial_DIN0207_L6.3mm_D2.5mm_P7.62mm_Horizontal,
100kΩ 1/4W,1,R5,R_Axial_DIN0207_L6.3mm_D2.5mm_P7.62mm_Horizontal,
10kΩ(未実装),1,R6,R_Axial_DIN0207_L6.3mm_D2.5mm_P7.62mm_Horizontal,本体に /IRQ のプルアップが無い時だけ付ける
0Ω(ジャンパー線でも可),1,R7,R_Axial_DIN0207_L6.3mm_D2.5mm_P7.62mm_Horizontal,音声 45→46番の素通し
47kΩ,1,R8,R_Axial_DIN0207_L6.3mm_D2.5mm_P7.62mm_Horizontal,拡張音源を46番に混ぜる抵抗(VR1 の中点から)
1kΩ 1/4W,1,R9,R_Axial_DIN0207_L6.3mm_D2.5mm_P7.62mm_Horizontal,
47kΩ 1/4W,1,R10,R_Axial_DIN0207_L6.3mm_D2.5mm_P7.62mm_Horizontal,
100Ω 1/4W,1,R11,R_Axial_DIN0207_L6.3mm_D2.5mm_P7.62mm_Horizontal,
タクトスイッチ 6mm,1,SW1,SW_PUSH_6mm,BOOTSEL
タクトスイッチ 6mm,1,SW2,SW_PUSH_6mm,RESET(RP2350のRUN)
74LVC245 DIP-20,1,U2,DIP-20_W7.62mm,SN74LVC245AN。5V入力を3.3Vへ。74HC/HCT245 では代用不可(5V入力に耐えない)
半固定抵抗 100kΩ KOA KVSF637AC104,1,VR1,KOA_SF6_637A,拡張音源の音量。上面調整、足 ①③ 5.0mm・② は 5.0mm 上
Waveshare Core2350B2,1,U1,,RP2350B、2MB PSRAM。付属のFPC-USBアダプターで PC とつなぐ
ピンソケット 2x8(2.54mm),4,P1-P4,,Core2350B を載せる。モジュール側には 2x8 ピンヘッダー4個
ピンヘッダー 2x8(2.54mm),4,(モジュール側),,Core2350B の裏に付ける
ICソケット DIP-20,1,(U2),,任意
PCB 90x65.8mm 2層 1.2mm,1,,,金メッキ端子(Gold fingers)、差し込み側 45°面取り

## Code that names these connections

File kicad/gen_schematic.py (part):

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
  J1  ファミコン カセット端子 60ピン(基板エッジ)
  P1-P4  Waveshare Core2350B(RP2350B)の 8x2 ヘッダー4列
  U2  74LVC245  PPU /RD・/WR・A13 を 5V→3.3V(5V非トレラントの GPIO40-42 へ)
  Q1  NPN(2SC1815等)  /IRQ をオープンコレクタで引く
  J2  3.5mm ライン出力 / J3 SWD

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# 信号線は ../../FC のダンパー(fc_uno / fc_nano / fc_chr328)で実機確認済みの対応。
# 1,16(GND) 30,31(+5V) 15(/IRQ) 18(CIRAM A10) 45,46(音声) 47(/WR) 48(CIRAM /CE) 49(/A13) は
# nesdev の資料による。基板発注前に麻雀カセット・本体で導通確認すること。
FC_PINS = {1: "GND", 2: "CPU_A11", 3: "CPU_A10", 4: "CPU_A9", 5: "CPU_A8", 6: "CPU_A7", 7: "CPU_A6",
           8: "CPU_A5", 9: "CPU_A4", 10: "CPU_A3", 11: "CPU_A2", 12: "CPU_A1", 13: "CPU_A0", 14: "CPU_R~{W}",
           15: "~{IRQ}", 16: "GND", 17: "PPU_~{RD}", 18: "CIRAM_A10", 19: "PPU_A6", 20: "PPU_A5", 21: "PPU_A4",
           22: "PPU_A3", 23: "PPU_A2", 24: "PPU_A1", 25: "PPU_A0", 26: "PPU_D0", 27: "PPU_D1", 28: "PPU_D2",
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    return out


P1_NAMES = _gpio_header(0)     # GPIO0-14
P3_NAMES = _gpio_header(15)    # GPIO15-29
P4_NAMES = _gpio_header(30)    # GPIO30-44
P2_NAMES = ["GND", "GPIO45", "GPIO47_PSRAM_CS", "GPIO46", "BOOTSEL", "SWD", "USBD_N", "GND",
            "USBD_P", "SWCLK", "RUN", "ADC_VREF", "3V3_EN", "GND", "VBUS", "3V3"]


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           f'(stroke (width 0.254) (type default)) (fill (type background))))',
           f'(symbol "{name}_1_1"']
    for num, pname, ptype, x, y, ang in pins:
        out.append(f'(pin {ptype} line (at {fmt(x)} {fmt(y)} {ang}) (length {G}) '
                   f'(name "{pname}" {FONT}) (number "{num}" {FONT}))')
    out.append("))")
    return "\n".join(out), pins
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           f'(symbol "{name}_0_1" {body})',
           f'(symbol "{name}_1_1"']
    for num, pname, ptype, x, y, ang in pins:
        out.append(f'(pin {ptype} line (at {fmt(x)} {fmt(y)} {ang}) (length 1.27) (name "{pname}" {FONT}) (number "{num}" {FONT}))')
    out.append("))")
    return "\n".join(out), pins

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

# ---- ピン割り当て(GPIO → ネット) ----------------------------------------------
# PIO の 32本窓: CPU用ブロックは GPIO0-31、PPU用ブロックは GPIO16-47 を使う。
GPIO = {}
for i in range(8):
    GPIO[i] = f"CPU_D{i}"            # GPIO0-7
for i in range(15):
    GPIO[8 + i] = f"CPU_A{i}"        # GPIO8-22(A0から連続 = アドレスをそのまま添字にできる)
GPIO[23] = "~{ROMSEL}"
GPIO[24] = "CPU_R~{W}"
GPIO[25] = "M2"
for i in range(8):
    GPIO[26 + i] = f"PPU_D{i}"       # GPIO26-33: PPU AD0-7(/RD直前はアドレス下位、その後データ)
for i in range(5):
    GPIO[34 + i] = f"PPU_A{8 + i}"   # GPIO34-38: 26-38 で13ビットのアドレスが連続する
# GPIO39 = 基板上LED(470Ω)。バス信号には使わない
GPIO[40] = "PPU_~{RD}_3V3"           # GPIO40-44 は5V非トレラント → 74LVC245 経由の入力か出力専用
GPIO[41] = "PPU_~{WR}_3V3"
GPIO[42] = "PPU_A13_3V3"
GPIO[43] = "CIRAM_A10_MCU"
GPIO[44] = "EXP_AUDIO_PWM"
GPIO[45] = "IRQ_DRV"
GPIO[46] = "FC_5V_SENSE"

# J1 カセット端子(ラベル名は FC_PINS と同じ。電源だけ名前を合わせる)
# PPU A0-A7(ラッチ出力)は RP2350 では使わない(AD0-7から読む)が、J4 のブレイクアウトには出す
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                nets[str(pin)] = ""      # LED
    place(sym, ref, f"Core2350B {ref}", x, y, nets)

p2 = {"1": "GND", "8": "GND", "14": "GND", "2": GPIO[45], "4": GPIO[46], "5": "BOOTSEL", "11": "RUN",
      "6": "SWD", "10": "SWCLK", "15": "VBUS_MOD", "16": "+3V3",
      "7": "USBD_N", "9": "USBD_P"}   # USB はモジュールの FPC でも使っている。J6 は予備のランド(同時に機器をつながない)
place("Core2350B_P2", "P2", "Core2350B P2", G * 128, G * 24, p2)
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place("R", "R2", "15k", G * 122, G * 100, {"1": "+5V", "2": "FC_5V_SENSE"})
place("R", "R3", "22k", G * 128, G * 100, {"1": "FC_5V_SENSE", "2": "GND"})

# /IRQ: GPIO45=H で Q1 がONし /IRQ を Low に引く(オープンコレクタ)
place("R", "R4", "4.7k", G * 146, G * 14, {"1": "IRQ_DRV", "2": "Q1_B"})
place("R", "R5", "100k", G * 151, G * 14, {"1": "Q1_B", "2": "GND"})
place("NPN_ECB", "Q1", "2SC1815", G * 151, G * 28, {"3": "Q1_B", "2": "~{IRQ}", "1": "GND"})
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text("FC-MAGICON: Waveshare Core2350B (RP2350B) Famicom cartridge - PRG/CHR emulation, NSF, screen streaming",
     G * 8, G * 8, 2.5)
notes = [
    "GPIO0-38 are 5V tolerant (IOVDD must be powered). GPIO40-47 are ADC pins: NOT 5V tolerant -> via U2 or output only.",
    "PPU A0-A7 (cart 19-25, 50) are NOT used: low address is sampled on PPU_D0-7 (=PPU AD0-7) just before /RD falls.",
    "GPIO39 has the on-board LED (470R) - keep it off the bus. GPIO47 = on-board PSRAM CS.",
    "RP2350 erratum E9: do not enable internal pull-downs on bus pins.",
    "Close exactly one of JP1/JP2/JP3 (CIRAM A10 source).",
    "Firmware must keep all bus pins as inputs until FC_5V_SENSE is high (USB-only power must not back-power the console).",
    "Cart pins 1,16,30,31,15,18,45,46,47,48,49: nesdev docs, cross-checked with fc-rom-vomitter (51 signal pins verified on real carts).",
    "Q1 2SC1815 pin order E-C-B (flat face). R6 is DNP unless the console has no /IRQ pull-up.",
    "R8 (mix level) and R7 (pass-through) values are to be tuned on real hardware.",
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
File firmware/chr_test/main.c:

// FC-MAGICON chr_test — PPU 側(CHR)の応答を確かめるファームウェア
//
//   ・CPU バス: テスト ROM(chr_rom.h)を返す。ROM はパレットとネームテーブルを書いて背景を表示し、音を鳴らす
//   ・PPU バス: パターンテーブル $0000-$1FFF の読み出しに、ここで作った CHR を返す
//       タイル t = 下位2ビットの色で塗り、上辺(1行目)と左端(1列目)は色1の格子線
//       → 画面に「4色の縦縞 + 8ドットごとの格子」が出れば、/RD 直前に AD0-7 から読む下位アドレスは正しい
//   ・CIRAM A10(GPIO43)は Low に固定(JP1 を閉じた場合は1画面ミラー。JP2/JP3 の場合は関係ない)
//
// 応答はコア1が CPU と PPU の両方の FIFO を見て返す(割り込みなし)。PPU を優先する。
// USB シリアルに 1 秒ごとの CPU・PPU の読み出し回数を出す(PPU は表示中およそ 530 万回/秒の見込み)。
#include <stdio.h>
#include "../power_guard.h"
#include "pico/stdlib.h"
#include "pico/multicore.h"
#include "hardware/pio.h"
#include "hardware/clocks.h"
#include "hardware/vreg.h"
#include "cpu_bus.pio.h"
#include "ppu_chr.pio.h"
#include "chr_rom.h"

#define PIN_RW        24
#define PIN_LED       39
#define PIN_CIRAM_A10 43
#define PIN_FC_5V     46
#define BUS_PIN_LAST  42

static volatile uint32_t n_cpu, n_ppu, n_ppu_nt;
static uint8_t prg[0x8000];
static uint8_t chr[0x2000];

static void __not_in_flash_func(bus_loop)(void) {
    PIO cpu = pio0, ppu = pio1;
    uint32_t writes = 0;
    for (;;) {
        if (!pio_sm_is_rx_fifo_empty(ppu, 0)) {              // PPU を先に(こちらの方が速い)
            uint32_t v = ppu->rxf[0];
            if (v & (1u << 16)) {                            // A13 = 1: ネームテーブル(本体の VRAM が出す)
                ppu->txf[0] = 0x80000000u;
                n_ppu_nt++;
            } else {
                ppu->txf[0] = 0x8000FF00u | chr[v & 0x1FFF];     // AD0-7 + A8-12 = 13 ビットのアドレス
                n_ppu++;
            }
        }
        if (!pio_sm_is_rx_fifo_empty(cpu, 0)) {
            uint32_t v = cpu->rxf[0];
            if (v & (1u << PIN_RW)) {
                cpu->txf[0] = 0xFF00u | prg[(v >> 8) & 0x7FFF];
                n_cpu++;
            } else {
                cpu->txf[0] = 0;
                if ((++writes & 0xFFFF) == 0)
                    gpio_xor_mask64(1ull << PIN_LED);
            }
        }
    }
}

static void make_chr(void) {
    for (uint t = 0; t < 256; t++) {
        for (uint r = 0; r < 8; r++) {
            uint8_t p0 = (t & 1) ? 0xFF : 0x00;
            uint8_t p1 = (t & 2) ? 0xFF : 0x00;
            if (r == 0) { p0 = 0xFF; p1 = 0x00; }             // 上辺は色1
            else { p0 |= 0x80; p1 &= 0x7F; }                 // 左端も色1
            chr[t * 16 + r] = p0;                             // パターンテーブル 0
            chr[t * 16 + 8 + r] = p1;
        }
    }
    for (uint i = 0; i < 0x1000; i++)
        chr[0x1000 + i] = chr[i];                             // パターンテーブル 1 も同じ
}

static void bus_pins_input(void) {
    for (uint p = 0; p <= BUS_PIN_LAST; p++) {
        if (p == PIN_LED) continue;
        gpio_init(p);
        gpio_set_dir(p, GPIO_IN);
        gpio_disable_pulls(p);                                // RP2350 エラッタ E9
    }
    for (uint p = PIN_CIRAM_A10; p <= PIN_FC_5V; p++) {
        gpio_init(p);
        gpio_set_dir(p, GPIO_IN);
        gpio_disable_pulls(p);
    }
}

int main(void) {
    bus_pins_input();
    gpio_init(PIN_LED);
    gpio_set_dir(PIN_LED, GPIO_OUT);

    vreg_set_voltage(VREG_VOLTAGE_1_20);
    sleep_ms(10);
    set_sys_clock_khz(250000, true);

    for (uint i = 0; i < sizeof prg; i++)
        prg[i] = chr_test_rom[i % sizeof chr_test_rom];
    make_chr();

    bool usb_prepared = !gpio_get(PIN_FC_5V);
    if (usb_prepared) stdio_init_all();
    fc_wait_power();
    fc_arm_power_guard();
    gpio_put(PIN_LED, 0);
    gpio_put(PIN_CIRAM_A10, 0);
    gpio_set_dir(PIN_CIRAM_A10, GPIO_OUT);

    pio_set_gpio_base(pio0, 0);                              // CPU: GPIO0-31
    pio_set_gpio_base(pio1, 16);                             // PPU: GPIO16-47
    ppu_chr_program_init(pio1, 0, pio_add_program(pio1, &ppu_chr_program));
    cpu_bus_program_init(pio0, 0, pio_add_program(pio0, &cpu_bus_program));
    multicore_launch_core1(bus_loop);
    pio_sm_set_enabled(pio1, 0, true);
    if (!usb_prepared) stdio_init_all();

    printf("FC-MAGICON chr_test: CPU+PPU at 250MHz\n");
    uint32_t lc = 0, lp = 0, ln = 0;
    for (;;) {
        sleep_ms(1000);
        uint32_t c = n_cpu, p = n_ppu, n = n_ppu_nt;
        printf("cpu reads/s %lu  ppu chr/s %lu  ppu nt/s %lu\n",
               (unsigned long)(c - lc), (unsigned long)(p - lp), (unsigned long)(n - ln));
        lc = c; lp = p; ln = n;
    }
}
